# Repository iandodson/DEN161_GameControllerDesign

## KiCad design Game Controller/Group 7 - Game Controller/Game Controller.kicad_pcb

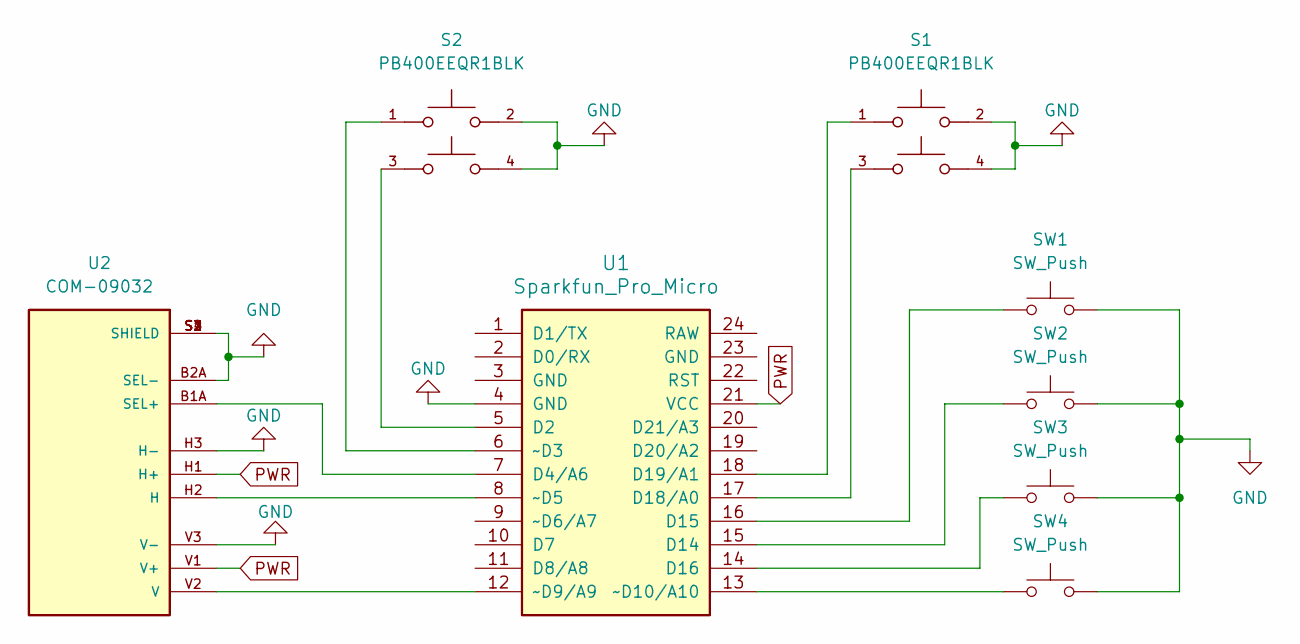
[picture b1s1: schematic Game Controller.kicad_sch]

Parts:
S1, S2: PB400EEQR1BLK; SW_PB400EEQR1BLK; PARTREV A
SW1, SW2, SW3, SW4: SW_Push; SW_Cherry_MX_1.00u_PCB
U1: Sparkfun_Pro_Micro
U2: COM-09032; XDCR_COM-09032; PARTREV N/A; DigiKey_Part_Number 1568-1526-ND

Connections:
GND: S1.2, S1.4, S2.2, S2.4, SW1.2, SW2.2, SW3.2, SW4.2, U1.4 (GND), U2.B2A (SEL-), U2.H3 (H-), U2.S1 (SHIELD), U2.S2 (SHIELD), U2.S3 (SHIELD), U2.S4 (SHIELD), U2.V3 (V-)
unnamed: S2.3, U1.5 (D2)
unnamed: U1.7 (D4/A6), U2.B1A (SEL+)
unnamed: SW2.1, U1.15 (D14)
unnamed: SW1.1, U1.16 (D15)
unnamed: SW3.1, U1.14 (D16)
unnamed: S1.3, U1.17 (D18/A0)
unnamed: S1.1, U1.18 (D19/A1)
unnamed: S2.1, U1.6 (~D3)
unnamed: U1.8 (~D5), U2.H2 (H)
unnamed: U1.12 (~D9/A9), U2.V2 (V)
unnamed: SW4.1, U1.13 (~D10/A10)
PWR: U1.21 (VCC), U2.H1 (H+), U2.V1 (V+)

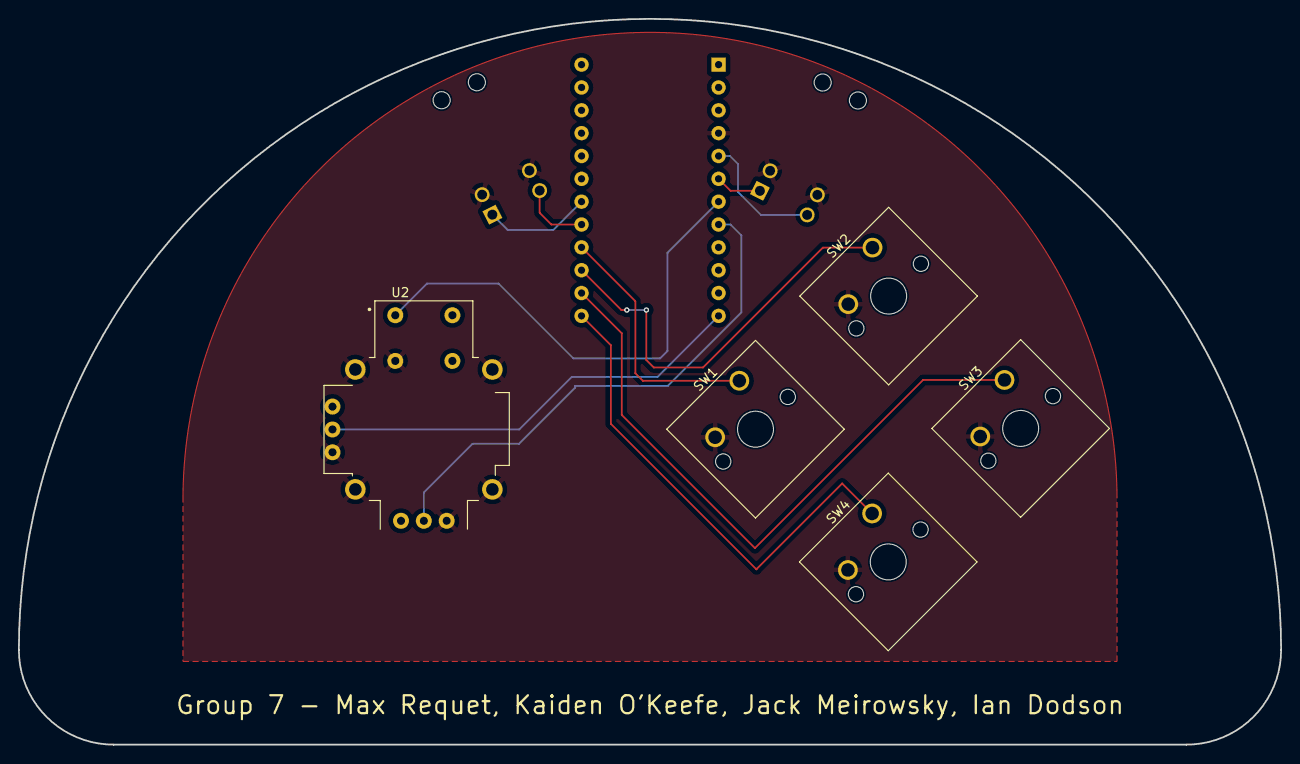
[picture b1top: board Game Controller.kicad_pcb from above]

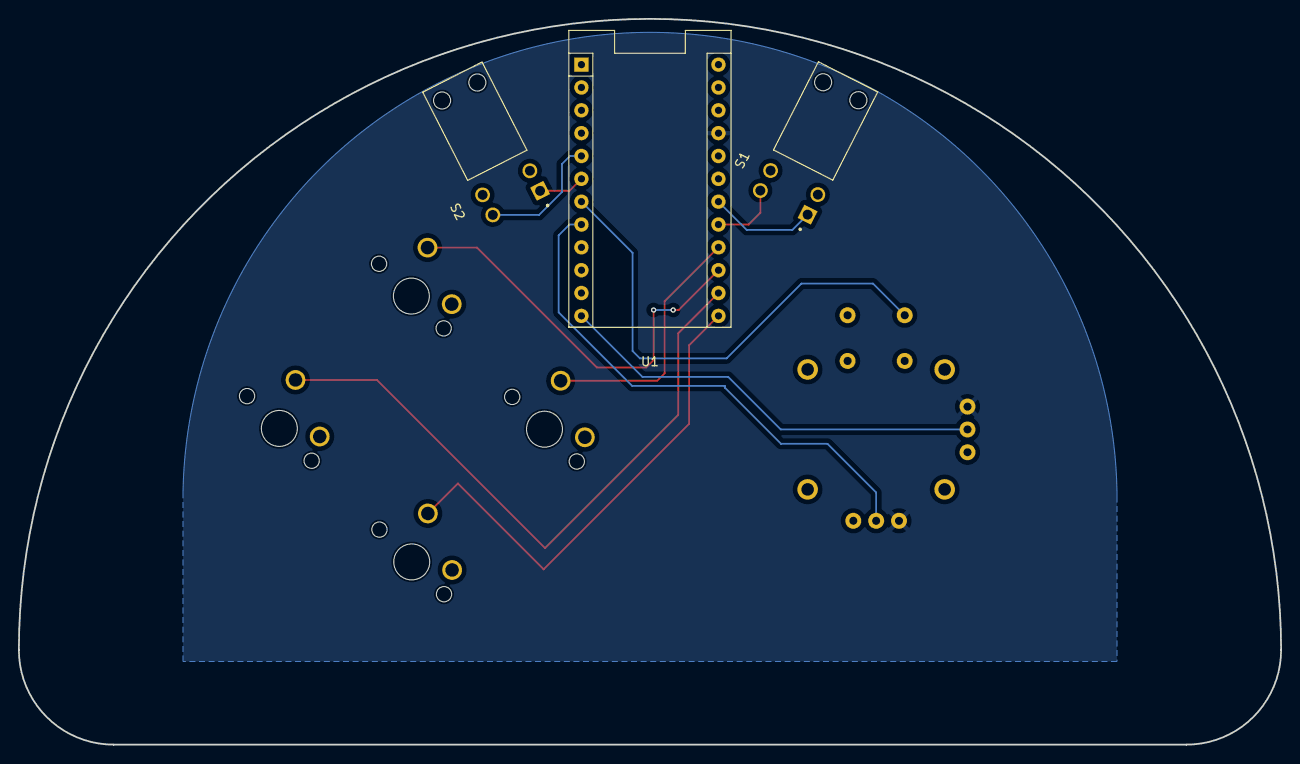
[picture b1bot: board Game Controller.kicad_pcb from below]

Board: 2 copper layers, 140.4 x 80.7 mm, 8 parts (3 on the bottom side), 13 nets.
